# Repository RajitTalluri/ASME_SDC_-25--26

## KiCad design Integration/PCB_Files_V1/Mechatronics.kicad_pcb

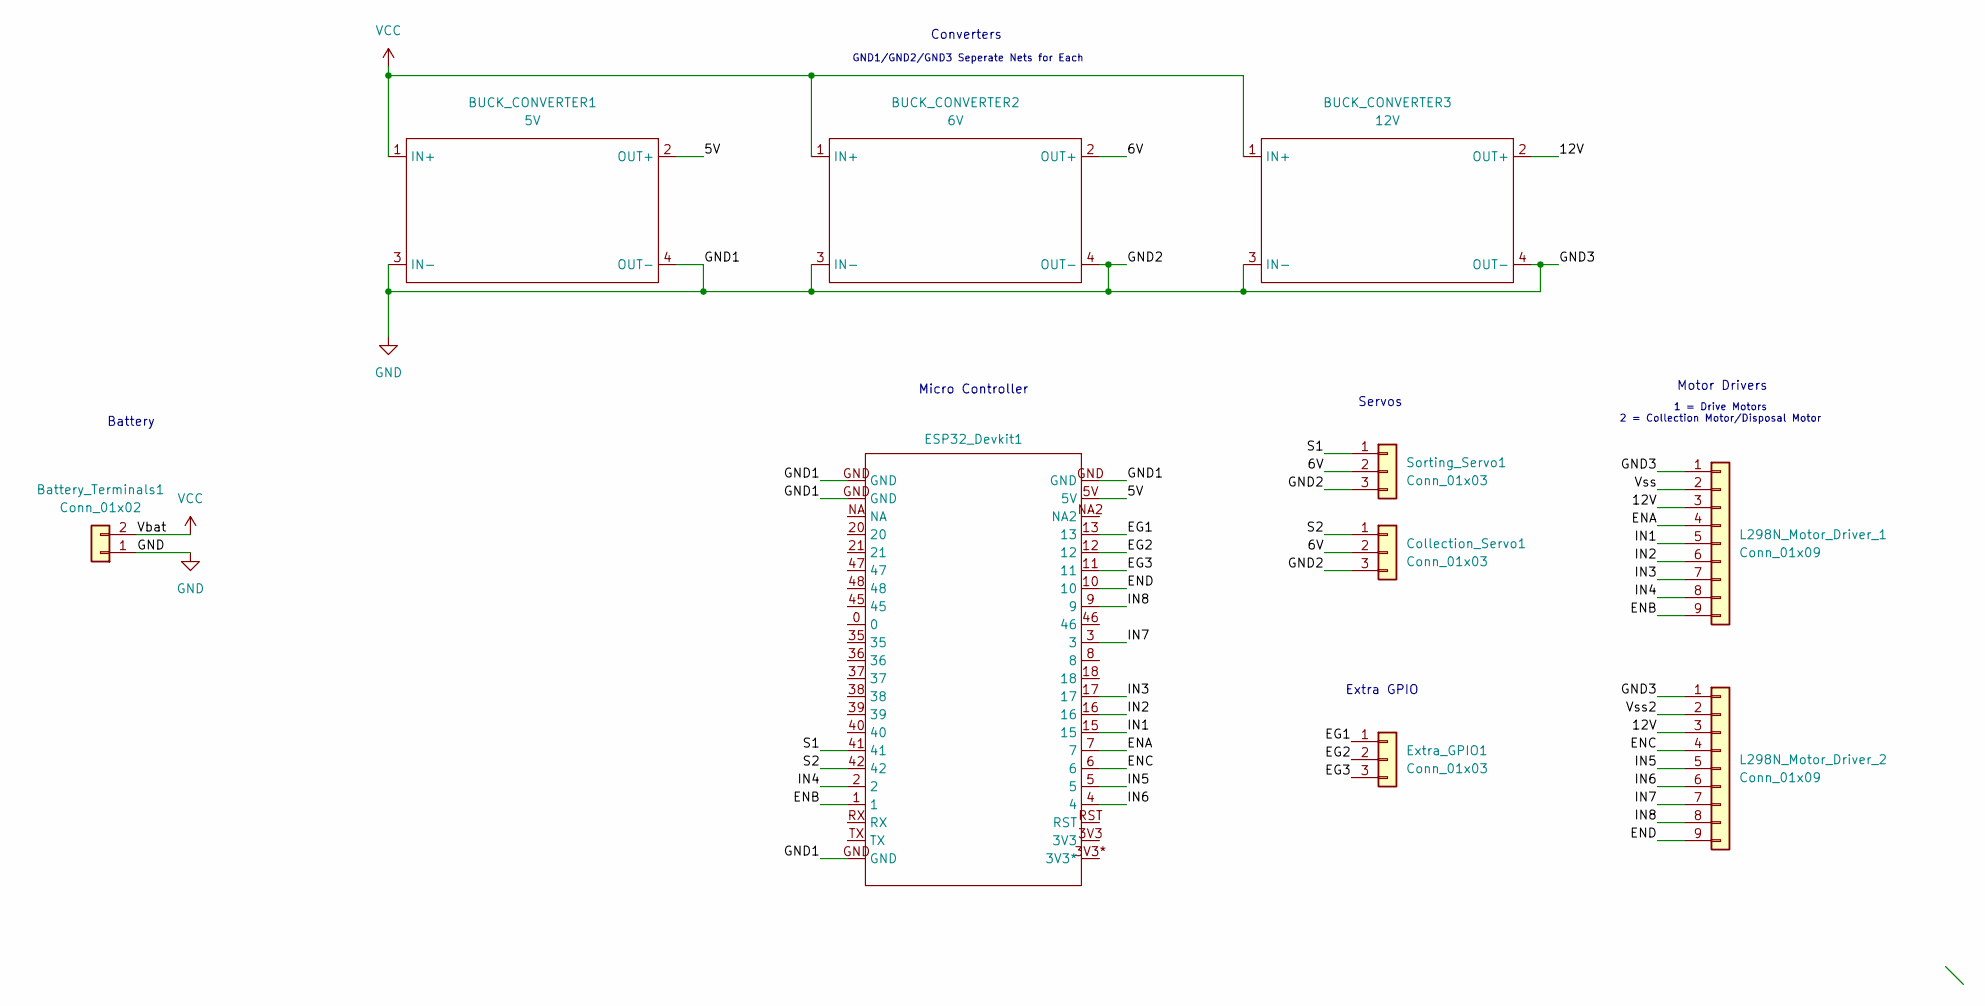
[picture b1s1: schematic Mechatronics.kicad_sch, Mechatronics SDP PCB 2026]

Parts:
BUCK_CONVERTER1: 5V; LM2596 BUCK CONVERTER MODULE
BUCK_CONVERTER2: 6V; LM2596 BUCK CONVERTER MODULE
BUCK_CONVERTER3: 12V; LM2596 BUCK CONVERTER MODULE
Battery_Terminals1: Conn_01x02; AMASS_XT60-F_1x02_P7.20mm_Vertical
Collection_Servo1: Conn_01x03; PinHeader_1x03_P2.54mm_Vertical
ESP32_Devkit1: ESP32DEVKIT
Extra_GPIO1: Conn_01x03; PinHeader_1x03_P2.54mm_Vertical
L298N_Motor_Driver_1, L298N_Motor_Driver_2: Conn_01x09; PinHeader_1x09_P2.54mm_Vertical
Sorting_Servo1: Conn_01x03; PinHeader_1x03_P2.54mm_Vertical

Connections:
/5V: BUCK_CONVERTER1.2 (OUT+), ESP32_Devkit1.5V
/6V: BUCK_CONVERTER2.2 (OUT+), Collection_Servo1.2, Sorting_Servo1.2
/12V: BUCK_CONVERTER3.2 (OUT+), L298N_Motor_Driver_1.3, L298N_Motor_Driver_2.3
/EG1: ESP32_Devkit1.13, Extra_GPIO1.1
/EG2: ESP32_Devkit1.12, Extra_GPIO1.2
/EG3: ESP32_Devkit1.11, Extra_GPIO1.3
/ENA: ESP32_Devkit1.7, L298N_Motor_Driver_1.4
/ENB: ESP32_Devkit1.1, L298N_Motor_Driver_1.9
/ENC: ESP32_Devkit1.6, L298N_Motor_Driver_2.4
/END: ESP32_Devkit1.10, L298N_Motor_Driver_2.9
/IN1: ESP32_Devkit1.15, L298N_Motor_Driver_1.5
/IN2: ESP32_Devkit1.16, L298N_Motor_Driver_1.6
/IN3: ESP32_Devkit1.17, L298N_Motor_Driver_1.7
/IN4: ESP32_Devkit1.2, L298N_Motor_Driver_1.8
/IN5: ESP32_Devkit1.5, L298N_Motor_Driver_2.5
/IN6: ESP32_Devkit1.4, L298N_Motor_Driver_2.6
/IN7: ESP32_Devkit1.3, L298N_Motor_Driver_2.7
/IN8: ESP32_Devkit1.9, L298N_Motor_Driver_2.8
/S1: ESP32_Devkit1.41, Sorting_Servo1.1
/S2: Collection_Servo1.1, ESP32_Devkit1.42
/Vss: L298N_Motor_Driver_1.2
/Vss2: L298N_Motor_Driver_2.2
GND: BUCK_CONVERTER1.3 (IN-), BUCK_CONVERTER1.4 (OUT-), BUCK_CONVERTER2.3 (IN-), BUCK_CONVERTER2.4 (OUT-), BUCK_CONVERTER3.3 (IN-), BUCK_CONVERTER3.4 (OUT-), Battery_Terminals1.1, Collection_Servo1.3, ESP32_Devkit1.GND, L298N_Motor_Driver_1.1, L298N_Motor_Driver_2.1, Sorting_Servo1.3
VCC: BUCK_CONVERTER1.1 (IN+), BUCK_CONVERTER2.1 (IN+), BUCK_CONVERTER3.1 (IN+), Battery_Terminals1.2

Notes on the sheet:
Micro Controller
Extra GPIO
Motor Drivers
Battery
1 = Drive Motors 2 = Collection Motor/Disposal Motor
Converters
GND1/GND2/GND3 Seperate Nets for Each
Servos

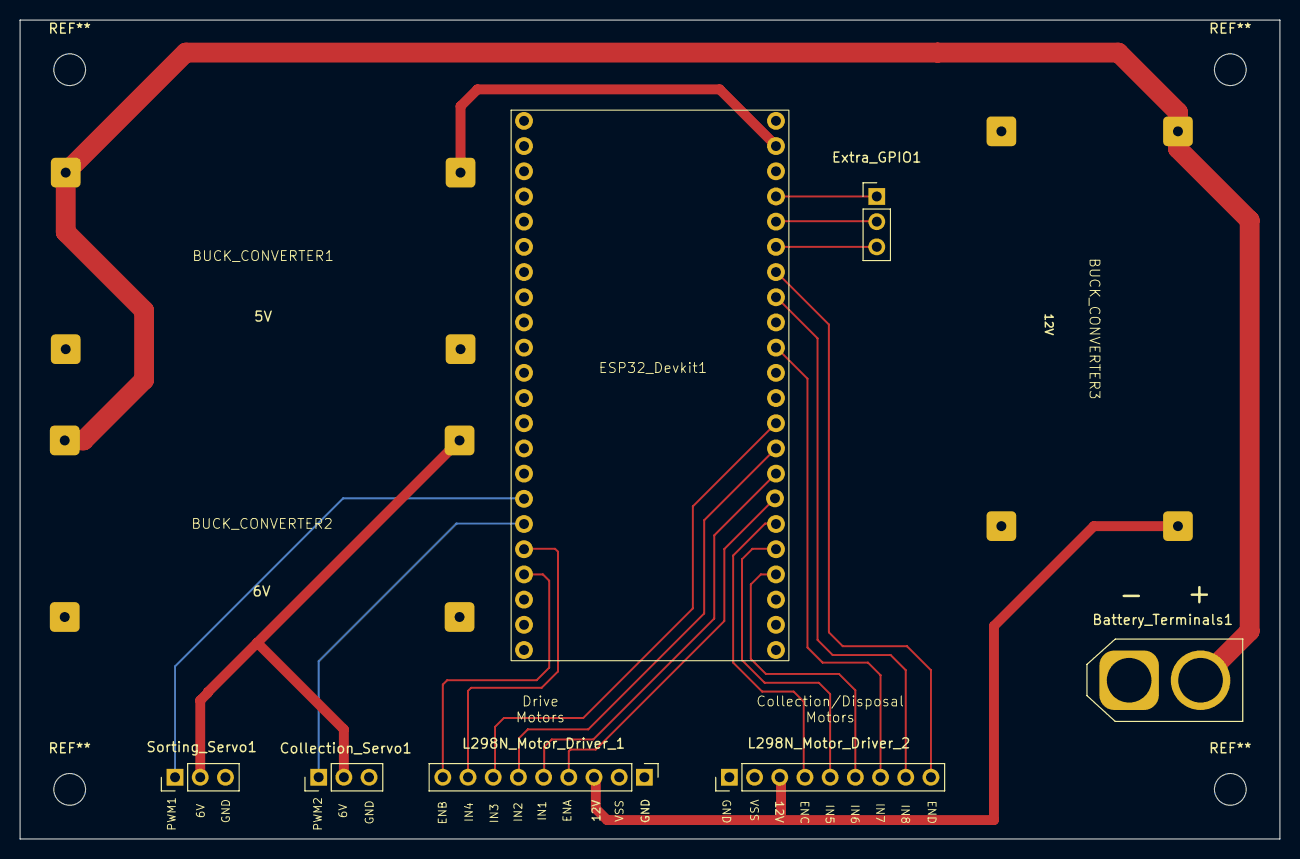
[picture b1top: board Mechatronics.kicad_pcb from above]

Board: 2 copper layers, 127.0 x 82.5 mm, 10 parts (0 on the bottom side), 22 nets.

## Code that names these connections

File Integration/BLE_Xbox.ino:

#include <Bluepad32.h>
#include <ESP32Servo.h>

ControllerPtr myController;

// EG - extra gpio 13,12,11
// EN - enable

// DEADZONES
int leftStickDzone = 50; // adjust as needed
int rightStickDzone = 50; // adjust as needed
int leftTriggerDzone = 50; // adjust as needed
int rightTriggerDzone = 50; // adjust as needed

// DRIVETRAIN - L298n MOTOR COTNROL
int LFmotorpin1 = 15; // In 1 pin
int LBmotorpin2 = 16; // In 2 pin
int LmotorENA = 7; // PWM, ENA pin

int RFmotorpin1 = 17; // In 3 pin
int RBmotorpin2 = 2; // In 4 pin
int RmotorENA = 1; // PWM, ENB pin

int Collectionmotorpin1 = 5; // In 5 pin
int Collectionmotorpin2 = 4; // In 6 pin
int CollectionmotorENA = 6; // PWM, ENC pin
int CollectionmotorSpeed = 255; // adjust as needed
int Disposalmotorpin1 = 3; // In 7 pin
int Disposalmotorpin2 = 9; // In 8 pin
int DisposalmotorENA = 10; // PWM, END pin
int CollectionmotorSpeed = 100; // slower for more torque


// SERVOS
Servo grabberServo;
int grabberServoPin = 41; // S1 labeled as PWM on PCB
Servo sorterServo;
int sorterServoPin = 42; // S2 labeled as PWM on PCB


// MOTOR HELPER FUNCTIONS
void ALLMotorSTOP(int maxSpeed) {
  digitalWrite(LFmotorpin1, LOW);
  digitalWrite(LBmotorpin2, LOW);
  analogWrite(LmotorENA, maxSpeed);
  
  digitalWrite(RFmotorpin1, LOW);
  digitalWrite(RBmotorpin2, LOW);
  analogWrite(RmotorENA, maxSpeed);
}


void leftPIVOT(int pivotSpeed) {
  digitalWrite(LFmotorpin1, HIGH); // L backward
  digitalWrite(LBmotorpin2, LOW);
  analogWrite(LmotorENA, pivotSpeed);

  digitalWrite(RFmotorpin1, HIGH); // R forward
  digitalWrite(RBmotorpin2, LOW);
  analogWrite(RmotorENA, pivotSpeed);
}


void rightPIVOT(int pivotSpeed) {
  digitalWrite(LFmotorpin1, LOW); // L forward
  digitalWrite(LBmotorpin2, HIGH);
  analogWrite(LmotorENA, pivotSpeed);

  digitalWrite(RFmotorpin1, LOW); // R backward
  digitalWrite(RBmotorpin2, HIGH);
  analogWrite(RmotorENA, pivotSpeed);
}


void setMotors(int leftSpeed, int rightSpeed) {
  if (leftSpeed > leftStickDzone) {
    digitalWrite(LFmotorpin1, LOW); // L forward
    digitalWrite(LBmotorpin2, HIGH);
    analogWrite(LmotorENA, leftSpeed);
  } else if (leftSpeed < -leftStickDzone) {
    digitalWrite(LFmotorpin1, HIGH); // L backward
    digitalWrite(LBmotorpin2, LOW);
    analogWrite(LmotorENA, -leftSpeed);
  } else {
    digitalWrite(LFmotorpin1, LOW);
    digitalWrite(LBmotorpin2, LOW);
    analogWrite(LmotorENA, 0);
  }


  if (rightSpeed > rightStickDzone) {
    digitalWrite(RFmotorpin1, HIGH); // R forward
    digitalWrite(RBmotorpin2, LOW);
    analogWrite(RmotorENA, rightSpeed);
  } else if (rightSpeed < -rightStickDzone) {
    digitalWrite(RFmotorpin1, LOW); // R backward
    digitalWrite(RBmotorpin2, HIGH);
    analogWrite(RmotorENA, -rightSpeed);
  } else {
    digitalWrite(RFmotorpin1, LOW);
    digitalWrite(RBmotorpin2, LOW);
    analogWrite(RmotorENA, 0);
  }
}


void onConnectedController(ControllerPtr ctl) {
  myController = ctl;
  Serial.println("Xbox controller connected");
}


void onDisconnectedController(ControllerPtr ctl) {
  myController = nullptr;
  Serial.println("Controller disconnected");
}


void setup() {
  Serial.begin(115200);
  delay(2000);
  BP32.setup(&onConnectedController, &onDisconnectedController);
  BP32.forgetBluetoothKeys();
  Serial.println("Waiting for controller...");

  pinMode(LFmotorpin1, OUTPUT);
  pinMode(LBmotorpin2, OUTPUT);
  pinMode(LmotorENA, OUTPUT);
  pinMode(RFmotorpin1, OUTPUT);
  pinMode(RBmotorpin2, OUTPUT);
  pinMode(RmotorENA, OUTPUT);
  pinMode(Collectionmotorpin1, OUTPUT);
  pinMode(Collectionmotorpin2, OUTPUT);
  pinMode(CollectionmotorENA, OUTPUT);
  pinMode(Disposalmotorpin1, OUTPUT);
  pinMode(Disposalmotorpin2, OUTPUT);
  pinMode(DisposalmotorENA, OUTPUT);
  ALLMotorSTOP(0);

  grabberServo.attach(grabberServoPin);
  grabberServo.write(90);
  sorterServo.attach(sorterServoPin); 
  sorterServo.write(90);
}


void loop() {
  BP32.update();

  if (!myController || !myController->isConnected()) {
    Serial.println("Controller not connected");
    delay(1000);
    return;
  }

  // Buttons
  if (myController->a()) {
    Serial.println("A");
    digitalWrite(Disposalmotorpin1, HIGH); // Disposal forward
    digitalWrite(Disposalmotorpin2, LOW);
    analogWrite(DisposalmotorENA, DisposalmotorSpeed);
  }        

  if (myController->b()) {
    {
    Serial.println("B");
    digitalWrite(Disposalmotorpin1, LOW);
    digitalWrite(Disposalmotorpin2, HIGH); // Disposal backward
    analogWrite(DisposalmotorENA, DisposalmotorSpeed);
  }        
  }
  if (myController->x())          Serial.println("X");
  if (myController->y())          Serial.println("Y");
  if (myController->l1()) {
    grabberServo.write(0); // Move grabber servo to 0 degrees (open)
    Serial.println("LB");
  }
  if (myController->r1()) {
    grabberServo.write(180); // Move grabber servo to 180 degrees (close)
    Serial.println("RB");
  }
  if (myController->l2())         Serial.println("LT");
  if (myController->r2())         Serial.println("RT");
  if (myController->thumbL())     Serial.println("Left Stick Click");
  if (myController->thumbR())     Serial.println("Right Stick Click");

  // DPad
  uint8_t dpad = myController->dpad();
  if (dpad & DPAD_UP) {
      digitalWrite(Collectionmotorpin1, HIGH); // Collection forward
      digitalWrite(Collectionmotorpin2, LOW);
      analogWrite(CollectionmotorENA, CollectionmotorSpeed);
      Serial.println("DPad Up");
  }    
  if (dpad & DPAD_DOWN) {
    digitalWrite(Collectionmotorpin1, LOW); // Collection backward
    digitalWrite(Collectionmotorpin2, HIGH);
    analogWrite(CollectionmotorENA, CollectionmotorSpeed);
    Serial.println("DPad Down");
  }
  if (dpad & DPAD_LEFT) {
    sorterServo.write(0); // Move sorter servo to 0 degrees (left)
    Serial.println("DPad Left");
  }
  if (dpad & DPAD_RIGHT) {
    sorterServo.write(180); // Move sorter servo to 180 degrees (right)
    Serial.println("DPad Right");
  }
  if (myController->miscHome())   Serial.println("Xbox Button");
  if (myController->miscStart())  Serial.println("Start/Menu");
  if (myController->miscSelect()) Serial.println("Select/View");

  // Analog sticks (only print if moved)
  int lx = myController->axisX();
  int ly = myController->axisY();
  int rx = myController->axisRX();
  int ry = myController->axisRY();

  // Drivetrain Pivots - LT and RT triggers for gradual speed control
  int lt = map(myController->brake(), 0, 1023, 0, 255); // Get LT trigger value (0-1023)
  int rt = map(myController->throttle(), 0, 1023, 0, 255); // Get LT trigger value (0-1023)

  if (lt > leftTriggerDzone) {  // LT trigger with deadzone
    leftPIVOT(lt);
  } else if (rt > rightTriggerDzone) {  // RT trigger with deadzone
    rightPIVOT(rt);
  } else if (abs(lx) > leftStickDzone || abs(ly) > leftStickDzone) {
      // Map sticks to -255 to 255 first
      int mappedY = map(ly, -512, 512, 255, -255); // inverted Y
      int mappedX = map(lx, -512, 512, -255, 255);
      int leftSpeed  = constrain(mappedY + mappedX, -255, 255);
      int rightSpeed = constrain(mappedY - mappedX, -255, 255);
    setMotors(leftSpeed, rightSpeed);
  } else {
    ALLMotorSTOP(0);
  }

  /*
  if (abs(lx) > leftDeadzone || abs(ly) > leftDeadzone) {  
    Serial.print("Left Stick X: "); Serial.print(lx);
    Serial.print(" Y: "); Serial.println(-ly);
  } */
  if (abs(rx) > rightStickDzone || abs(ry) > rightStickDzone) {
    Serial.print("Right Stick X: "); Serial.print(rx);
    Serial.print(" Y: "); Serial.println(-ry);
  }

  delay(100);
} 

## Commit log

2025-10-27 Remove unnecessary comments on LED pin usage
    Removed comments about sensor LED pin configuration.
2025-10-27 Clarify baud rate in serial initialization
    Added comment to clarify baud rate setting.
2025-12-09 Add files via upload
    Arduino Script that calibrates white then black at start to cater for different environments. High values across for white and low values across for black.
2025-12-09 Added delays to calibration section
    Added delays and improved calibration messages for clarity.
2025-12-09 Create ArduinoColorSensor
2025-12-09 add file for color sensor data to csv file
    This script collects RGB data from an Arduino and saves it to a CSV file. It allows users to mark object changes using the spacebar.
2025-12-09 Rename colorSensor_Auto_calibration.ino to colorsensor/colorSensor_Auto_calibration.ino
2025-12-16 Refactor labeling mode to support individual samples
    Updated labeling functionality to allow individual sample labeling instead of range-based labeling. Adjusted print statements for clarity and updated file handling for labeled data.
2025-12-18 Organize repo
2025-12-21 Add files via upload
    Total samples: 118
    Category distribution:
    neither: 58 samples (49.2%)
    green: 35 samples (29.7%)
    blue: 25 samples (21.2%)
2025-12-21 Data Handling
2025-12-21 Preprocessed data to be in 0-1 range and started script 3
2025-12-28 Chnaged labels to integer values and wrote training script
2025-12-29 Created System Diagram
2025-12-29 added diagram image
2025-12-29 Added model saving feature and data loss over time and accuracy over training
2025-12-29 Removed voltage bubbles
2025-12-29 Combined preprocessing 2.1 and 2.2 into single script. Fixed typos in file/folder names
2025-12-29 Created State Diagram
2025-12-29 Organized diagrams
2025-12-29 changed file name from 2 to 2.1
2025-12-31 Updated diagram
2026-01-19 Exporting weights as C arrays for ESP instead of saving model
2026-01-24 Guide to collect accurate data
2026-02-01 added scheduler to training
2026-02-01 Revise data collection procedure and sample guidelines
2026-02-03 Updated diagram, not complete yet
2026-02-03 New folder for integration
2026-02-03 Add ASME SDC Controller Comms Script
2026-02-04 Early stage BLE xbox script
2026-02-05 BLE script upload
2026-02-05 XBOX CONTROLLER SCRIPT - KC
2026-02-05 Initial script to rotate servo using xbox controller
2026-02-05 moved process input function before loop funciton
2026-02-12 Current Projected Button Mapping
2026-02-12 Updated XBox controller to Servo script
2026-02-12 Add Xbox BLE controller integration script
2026-02-18 Updated BLE_Xbox.ino
2026-02-18 updated BLE script
2026-02-19 test commit
2026-02-19 uodated diagram script
2026-02-19 updated ble_xbox script
2026-02-19 Working BLE_XBox Connection Script
2026-02-19 test
2026-02-19 Update controller button mapping for grabber and drivetrain
2026-02-19 Updated ControllerButtonMapping
2026-02-26 Added drivetrain functions to BLE script
2026-02-27 Made pivots analog and to trigger, added servo features
2026-02-27 added pin numnbers and collection dc motor driver
2026-03-11 updated button mappings
2026-03-11 same
2026-03-12 test3/11
2026-03-12 Updated mappings for pivot turn
2026-03-23 PCB_V1
    Need to reassign footprint and symbol library locations for ESP32 + Buck Converters
2026-03-24 Comments corrected
2026-03-30 Add files via upload
    Arduino script to control the sorting microservo.
2026-03-30 Added disposal dc motor control
2026-04-06 Updated pinouts
2026-04-06 Updated pinout
2026-04-06 updated comment
2026-04-06 Update motor pin assignments and speeds in BLE_Xbox
2026-04-08 reorganize: move diagram to documentation, create BLE_Controller folder
2026-04-08 reorganize: repo
2026-04-09 uploaded script from 04/08/2025
2026-04-09 uploaded script from 04/08
2026-04-09 Add BLE controller integration for drivetrain control
2026-04-15 Changed collection and disposal names
2026-04-16 Fixed drivetrain and added gradual steering
2026-04-23 Gradual controls for disposal and collection
2026-04-26 Wiring Code for GPIO Connections
2026-05-01 Winning Code
